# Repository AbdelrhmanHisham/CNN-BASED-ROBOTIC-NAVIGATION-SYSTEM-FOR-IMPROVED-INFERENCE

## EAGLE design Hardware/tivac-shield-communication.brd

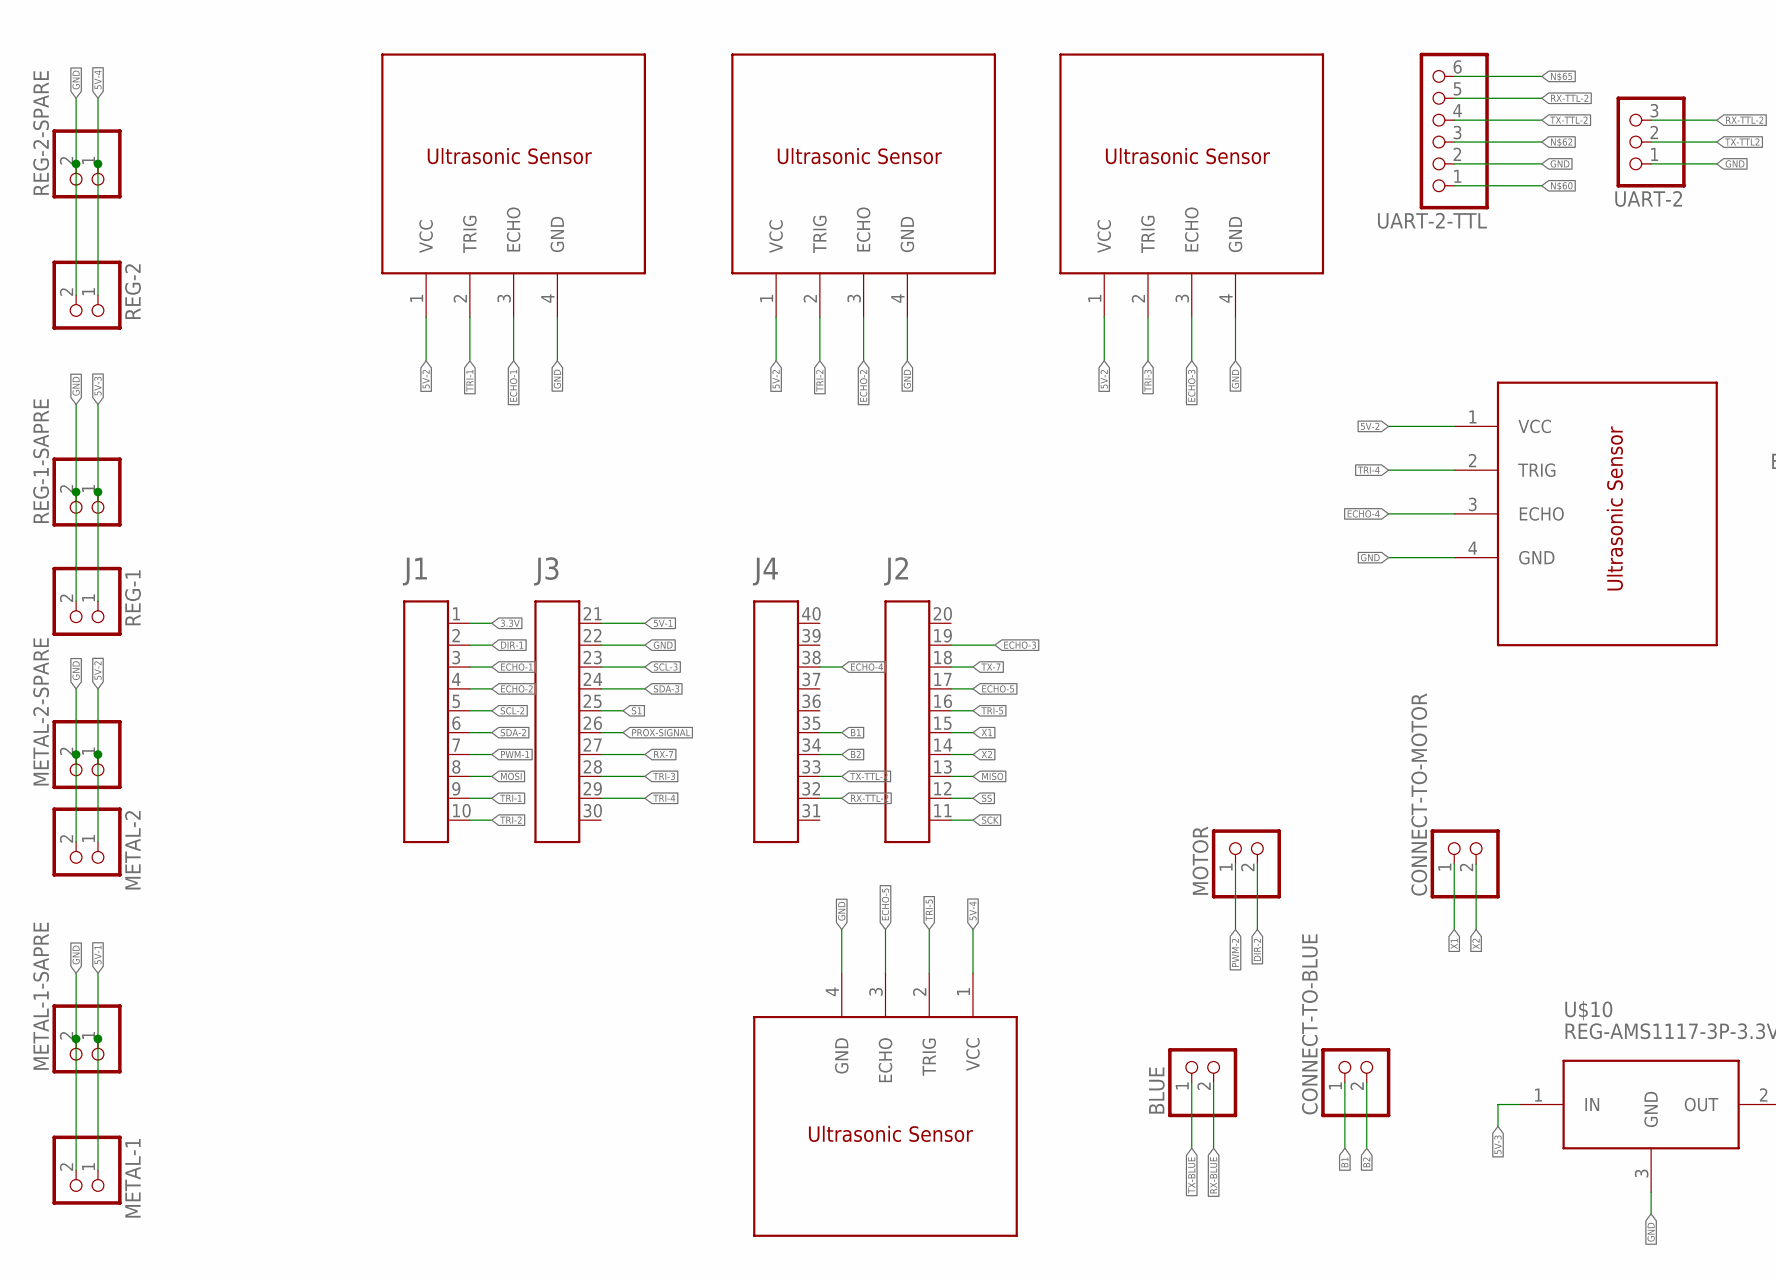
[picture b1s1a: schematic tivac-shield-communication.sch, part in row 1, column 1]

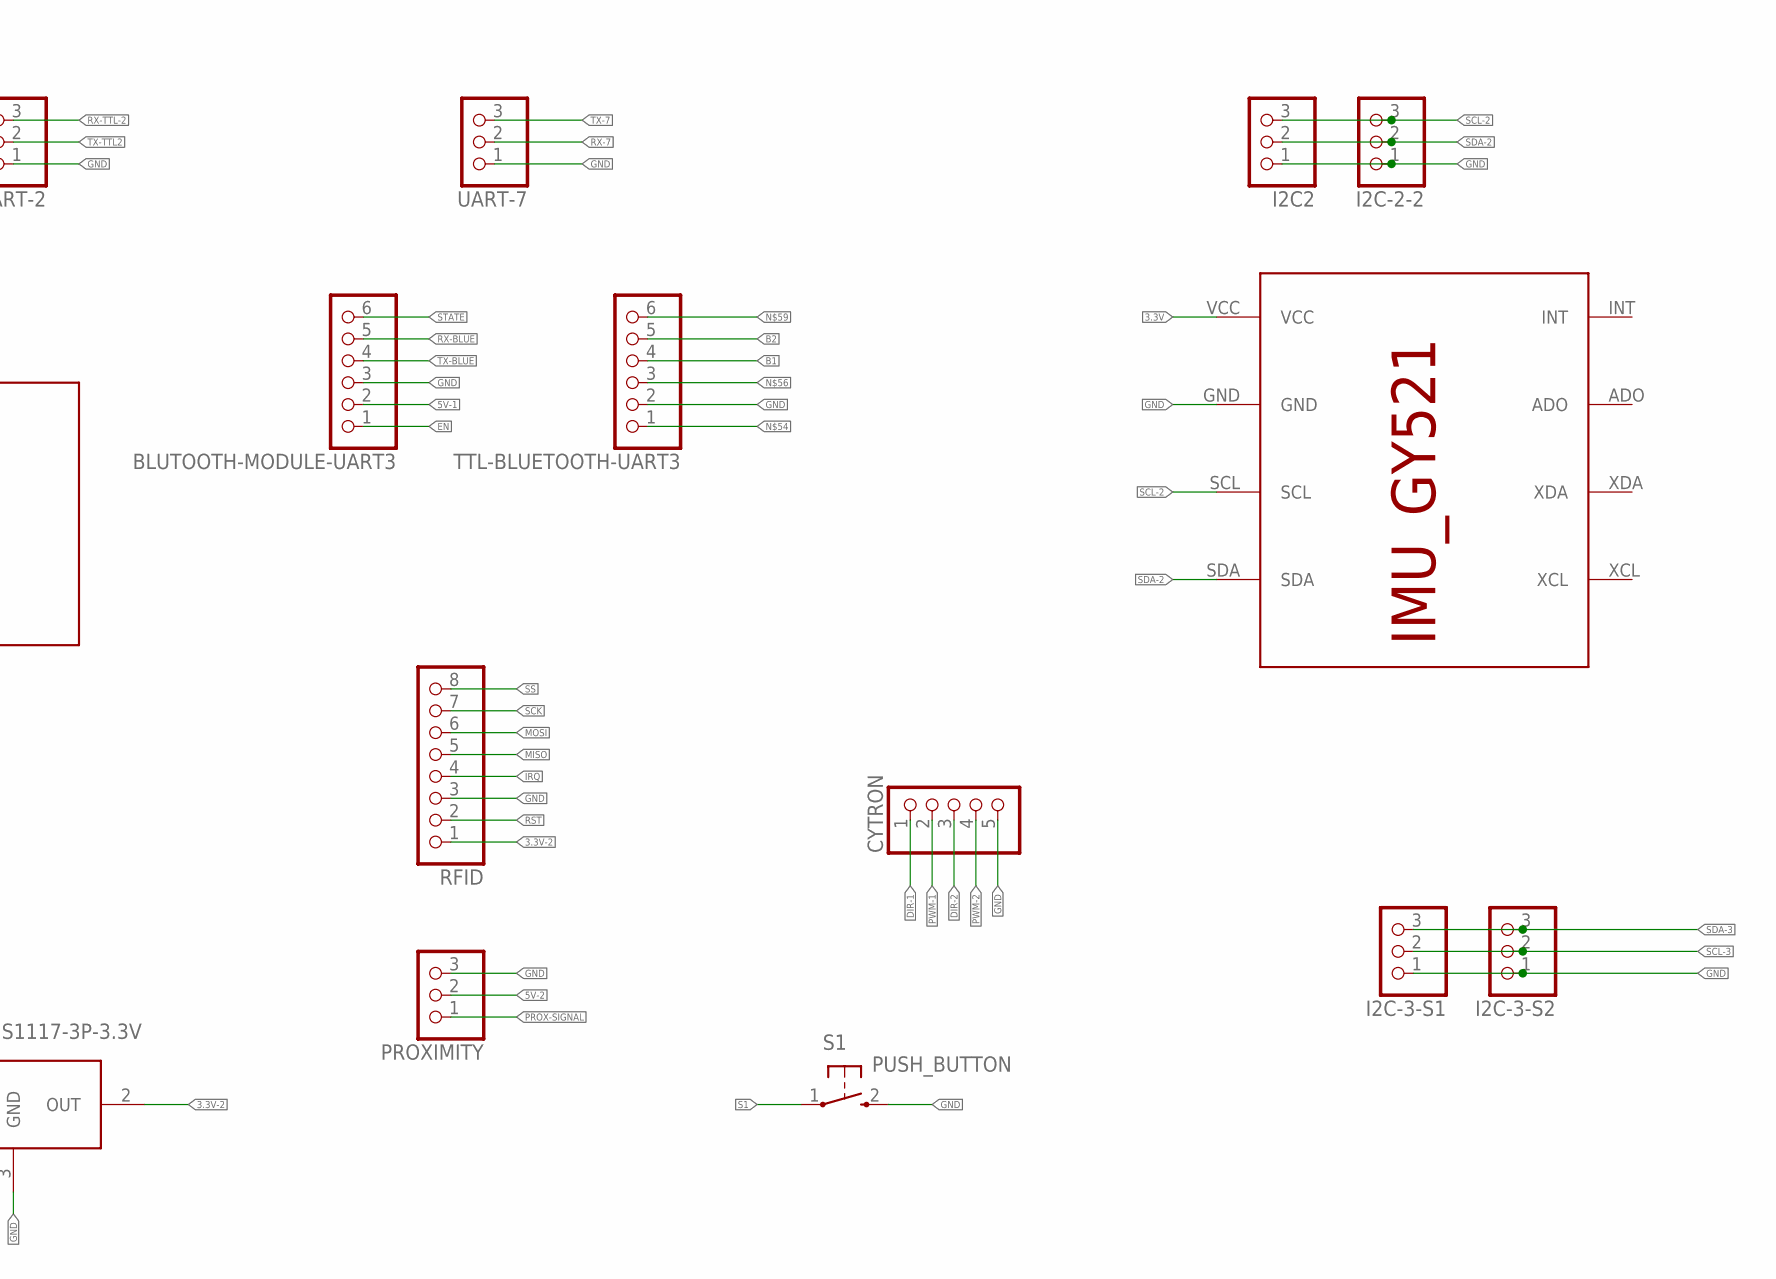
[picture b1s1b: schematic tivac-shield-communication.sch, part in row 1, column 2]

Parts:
A1: HEADER4X10-BOOSTERPACK; 4X10-BOOSTERPACK
BLUE: PINHD-2_DATA; 1X02_DATA
BLUTOOTH-MODULE-UART3: PINHD-1X6; 1X06
CONNECT-TO-BLUE: PINHD-2_DATA; 1X02_DATA
CONNECT-TO-MOTOR: PINHD-2_DATA; 1X02_DATA
CYTRON: PINHD-5_DATA; 1X05_DATA
I2C2, I2C-2-2, I2C-3-S1, I2C-3-S2: PINHD-1X3; 1X03
METAL-1, METAL-1-SAPRE, METAL-2, METAL-2-SPARE: PINHD-1X2; 1X02
MOTOR: PINHD-2_DATA; 1X02_DATA
PROXIMITY: PINHD-1X3; 1X03
REG-1, REG-1-SAPRE, REG-2, REG-2-SPARE: PINHD-1X2; 1X02
RFID: PINHD-1X8; 1X08
S1: PUSH_BUTTON; B3F-10XX
TTL-BLUETOOTH-UART3: PINHD-6_DATA; 1X06_DATA
U$1, U$2, U$3, U$5, U$7: ULTRASONIC_SENSOR; 1X04
U$9: IMU_ROBOCON; IMU_GY521
U$10: REG-AMS1117-3P-3.3V; REG-AMS1117-3P
UART-2, UART-7: PINHD-1X3; 1X03
UART-2-TTL: PINHD-6_DATA; 1X06_DATA

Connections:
3.3V: A1.1, U$9.VCC
3.3V-2: RFID.1, U$10.2 (OUT)
5V-1: A1.21, BLUTOOTH-MODULE-UART3.2, METAL-1.1, METAL-1-SAPRE.1
5V-2: METAL-2.1, METAL-2-SPARE.1, PROXIMITY.2, U$1.1 (VCC), U$2.1 (VCC), U$3.1 (VCC), U$7.1 (VCC)
5V-3: REG-1.1, REG-1-SAPRE.1, U$10.1 (IN)
5V-4: REG-2.1, REG-2-SPARE.1, U$5.1 (VCC)
B1: A1.35, CONNECT-TO-BLUE.1, TTL-BLUETOOTH-UART3.4
B2: A1.34, CONNECT-TO-BLUE.2, TTL-BLUETOOTH-UART3.5
DIR-1: A1.2, CYTRON.1
DIR-2: CYTRON.3, MOTOR.2
ECHO-1: A1.3, U$1.3 (ECHO)
ECHO-2: A1.4, U$2.3 (ECHO)
ECHO-3: A1.19, U$3.3 (ECHO)
ECHO-4: A1.38, U$7.3 (ECHO)
ECHO-5: A1.17, U$5.3 (ECHO)
EN: BLUTOOTH-MODULE-UART3.1
GND: A1.22, BLUTOOTH-MODULE-UART3.3, CYTRON.5, I2C2.1, I2C-2-2.1, I2C-3-S1.1, I2C-3-S2.1, METAL-1.2, METAL-1-SAPRE.2, METAL-2.2, METAL-2-SPARE.2, PROXIMITY.3, REG-1.2, REG-1-SAPRE.2, REG-2.2, REG-2-SPARE.2, RFID.3, S1.2 (S), TTL-BLUETOOTH-UART3.2, U$1.4 (GND), U$2.4 (GND), U$3.4 (GND), U$5.4 (GND), U$7.4 (GND), U$9.GND, U$10.3 (GND), UART-2.1, UART-2-TTL.2, UART-7.1
IRQ: RFID.4
MISO: A1.13, RFID.5
MOSI: A1.8, RFID.6
PROX-SIGNAL: A1.26, PROXIMITY.1
PWM-1: A1.7, CYTRON.2
PWM-2: CYTRON.4, MOTOR.1
RST: RFID.2
RX-7: A1.27, UART-7.2
RX-BLUE: BLUE.2, BLUTOOTH-MODULE-UART3.5
RX-TTL-2: A1.32, UART-2.3, UART-2-TTL.5
S1: A1.25, S1.1
SCK: A1.11, RFID.7
SCL-2: A1.5, I2C2.3, I2C-2-2.3, U$9.SCL
SCL-3: A1.23, I2C-3-S1.2, I2C-3-S2.2
SDA-2: A1.6, I2C2.2, I2C-2-2.2, U$9.SDA
SDA-3: A1.24, I2C-3-S1.3, I2C-3-S2.3
SS: A1.12, RFID.8
STATE: BLUTOOTH-MODULE-UART3.6
TRI-1: A1.9, U$1.2 (TRIG)
TRI-2: A1.10, U$2.2 (TRIG)
TRI-3: A1.28, U$3.2 (TRIG)
TRI-4: A1.29, U$7.2 (TRIG)
TRI-5: A1.16, U$5.2 (TRIG)
TX-7: A1.18, UART-7.3
TX-BLUE: BLUE.1, BLUTOOTH-MODULE-UART3.4
TX-TTL2: UART-2.2
TX-TTL-2: A1.33, UART-2-TTL.4
X1: A1.15, CONNECT-TO-MOTOR.1
X2: A1.14, CONNECT-TO-MOTOR.2

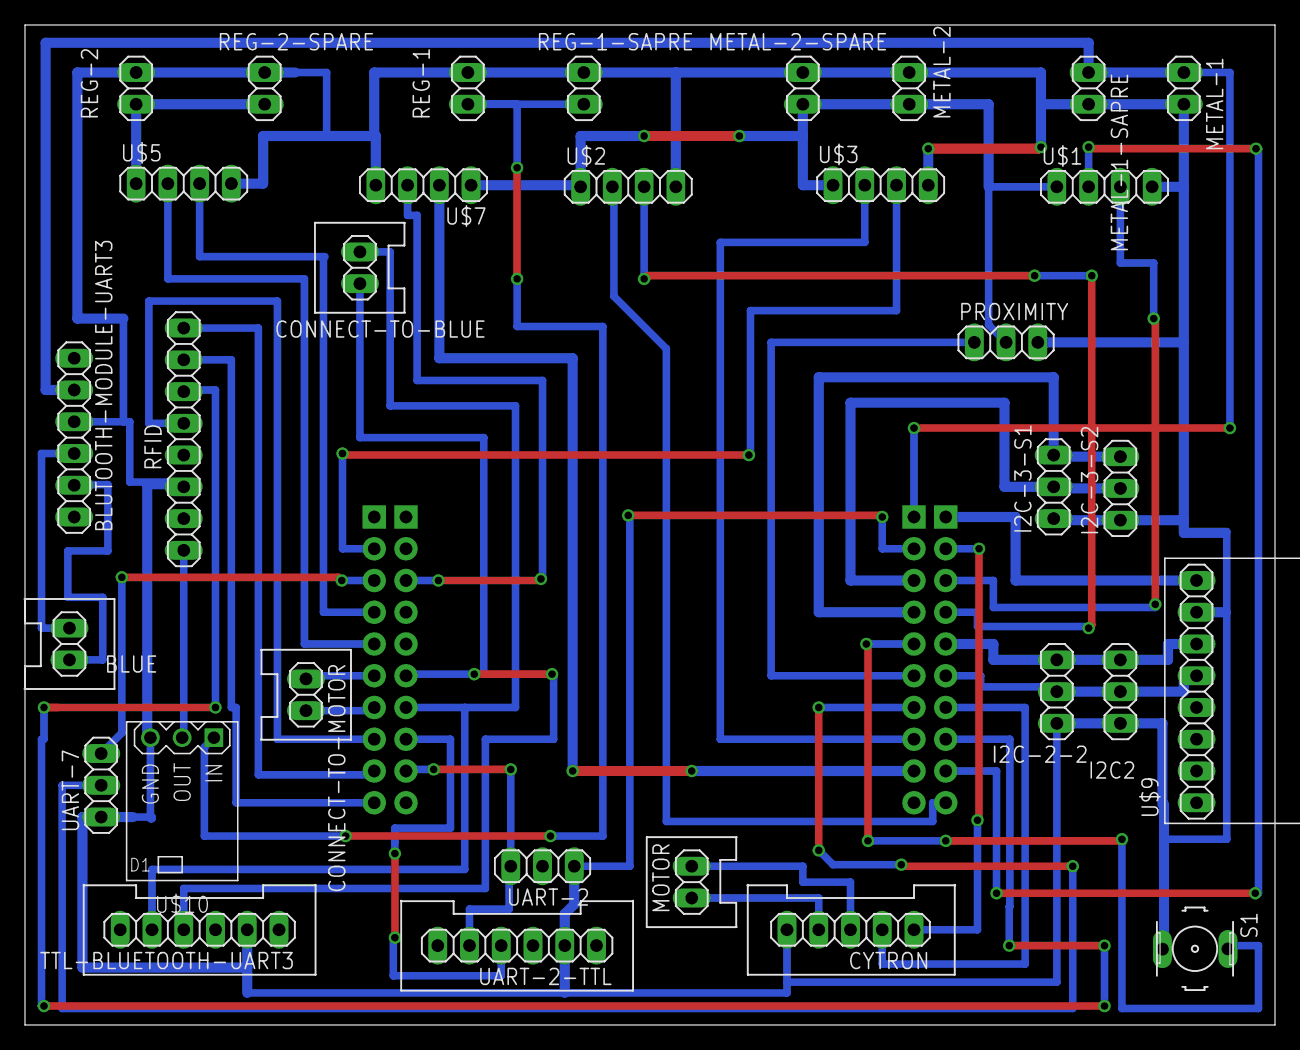
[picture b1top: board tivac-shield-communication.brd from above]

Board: 2 copper layers, 100.0 x 80.0 mm, 33 parts (1 on the bottom side), 41 nets.

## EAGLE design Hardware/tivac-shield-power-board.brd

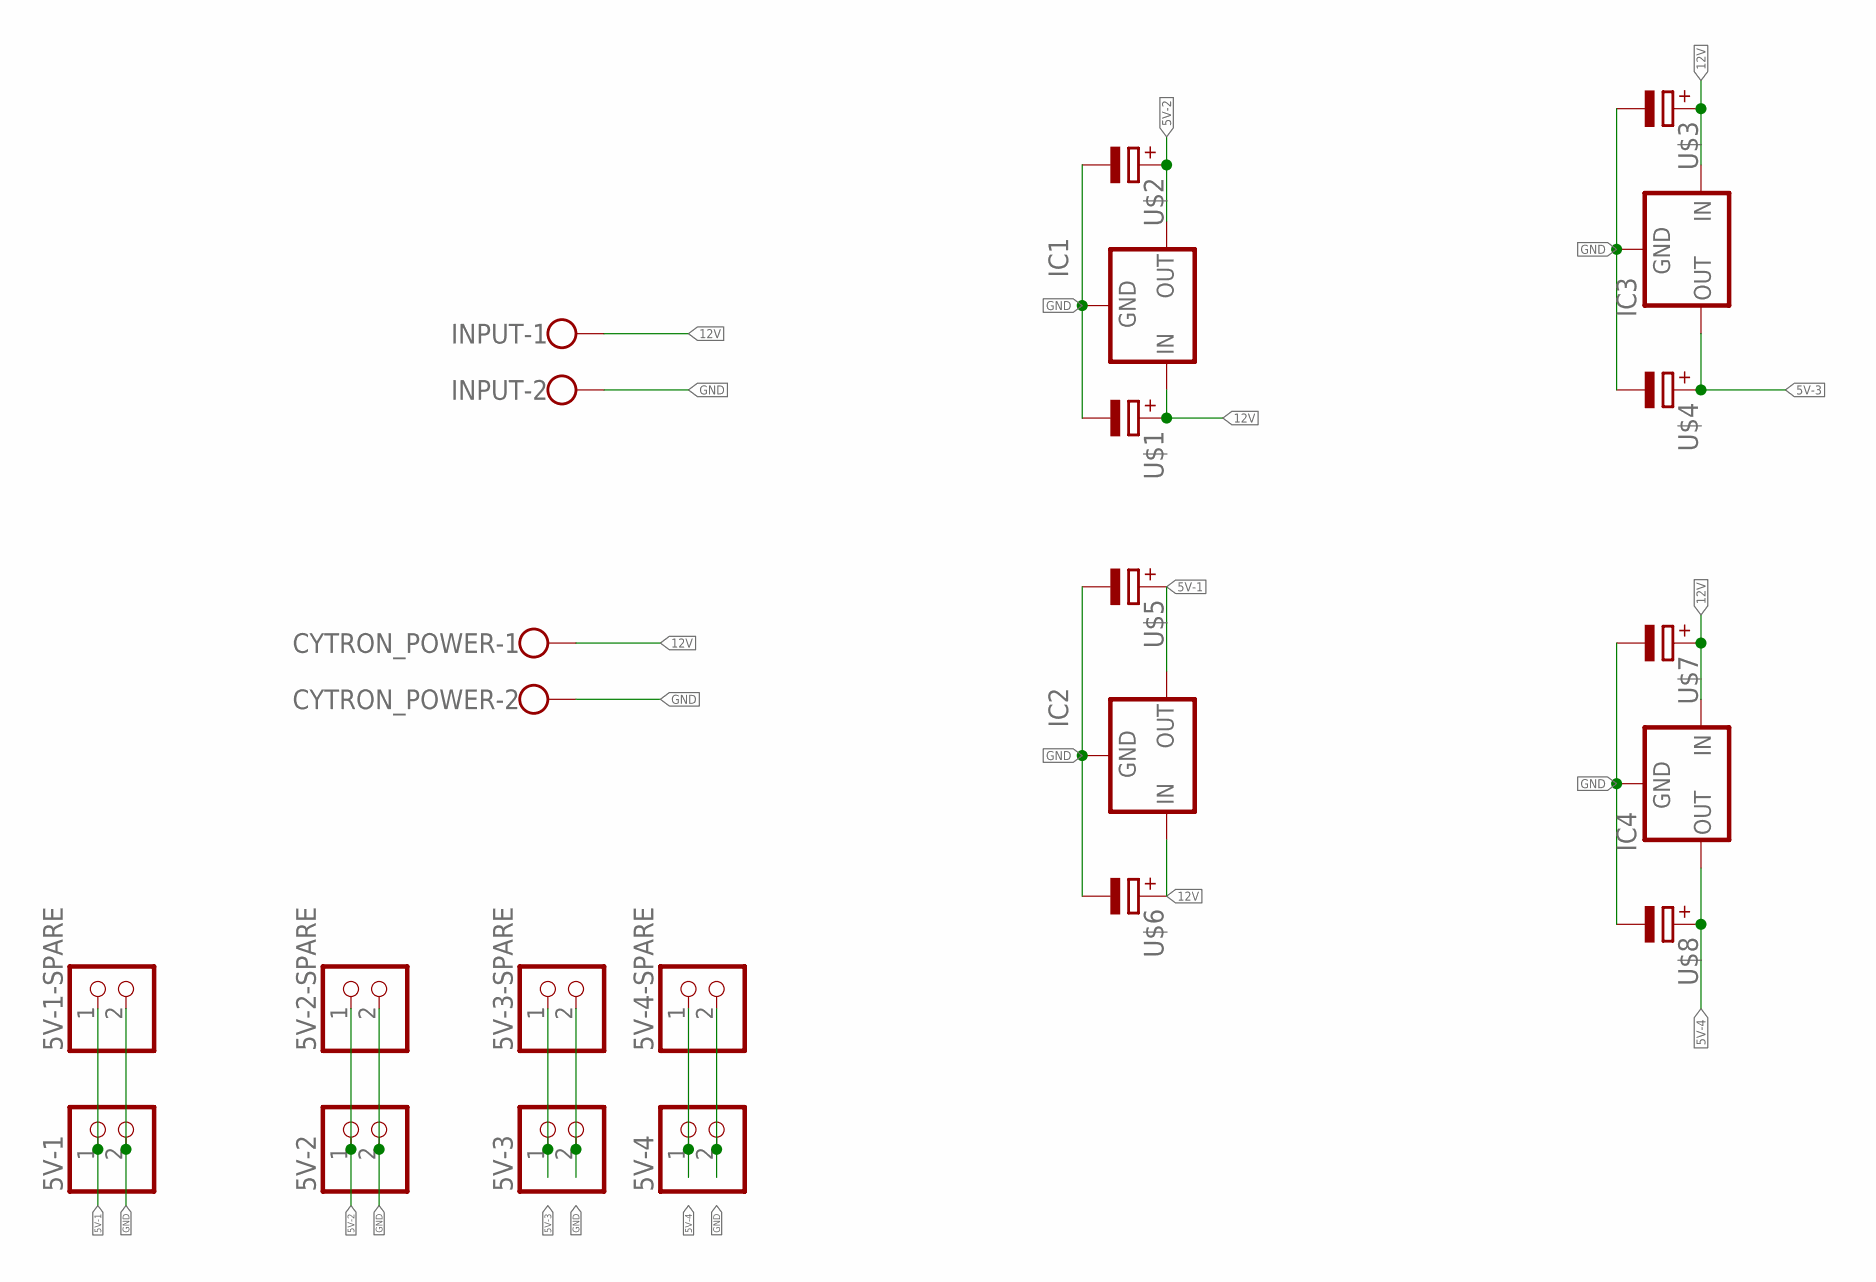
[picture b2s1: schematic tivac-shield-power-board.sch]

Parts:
5V-1, 5V-1-SPARE, 5V-2, 5V-2-SPARE, 5V-3, 5V-3-SPARE, 5V-4, 5V-4-SPARE: PINHD-1X2; 1X02
CYTRON_POWER: W237-113
IC1, IC2: 78XX-METAL; TO3-79
IC3, IC4: 78XXS
INPUT: W237-113
U$1, U$2, U$3, U$4, U$5, U$6, U$7, U$8: CAP_POL; E3,5-8

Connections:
5V-1: 5V-1.1, 5V-1-SPARE.1, IC2.1 (OUT), U$5.+
5V-2: 5V-2.1, 5V-2-SPARE.1, IC1.1 (OUT), U$2.+
5V-3: 5V-3.1, 5V-3-SPARE.1, IC3.OUT, U$4.+
5V-4: 5V-4.1, 5V-4-SPARE.1, IC4.OUT, U$8.+
12V: CYTRON_POWER.1, IC1.3 (IN), IC2.3 (IN), IC3.IN, IC4.IN, INPUT.1, U$1.+, U$3.+, U$6.+, U$7.+
GND: 5V-1.2, 5V-1-SPARE.2, 5V-2.2, 5V-2-SPARE.2, 5V-3.2, 5V-3-SPARE.2, 5V-4.2, 5V-4-SPARE.2, CYTRON_POWER.2, IC1.2 (GND), IC2.2 (GND), IC3.GND, IC4.GND, INPUT.2, U$1.-, U$2.-, U$3.-, U$4.-, U$5.-, U$6.-, U$7.-, U$8.-

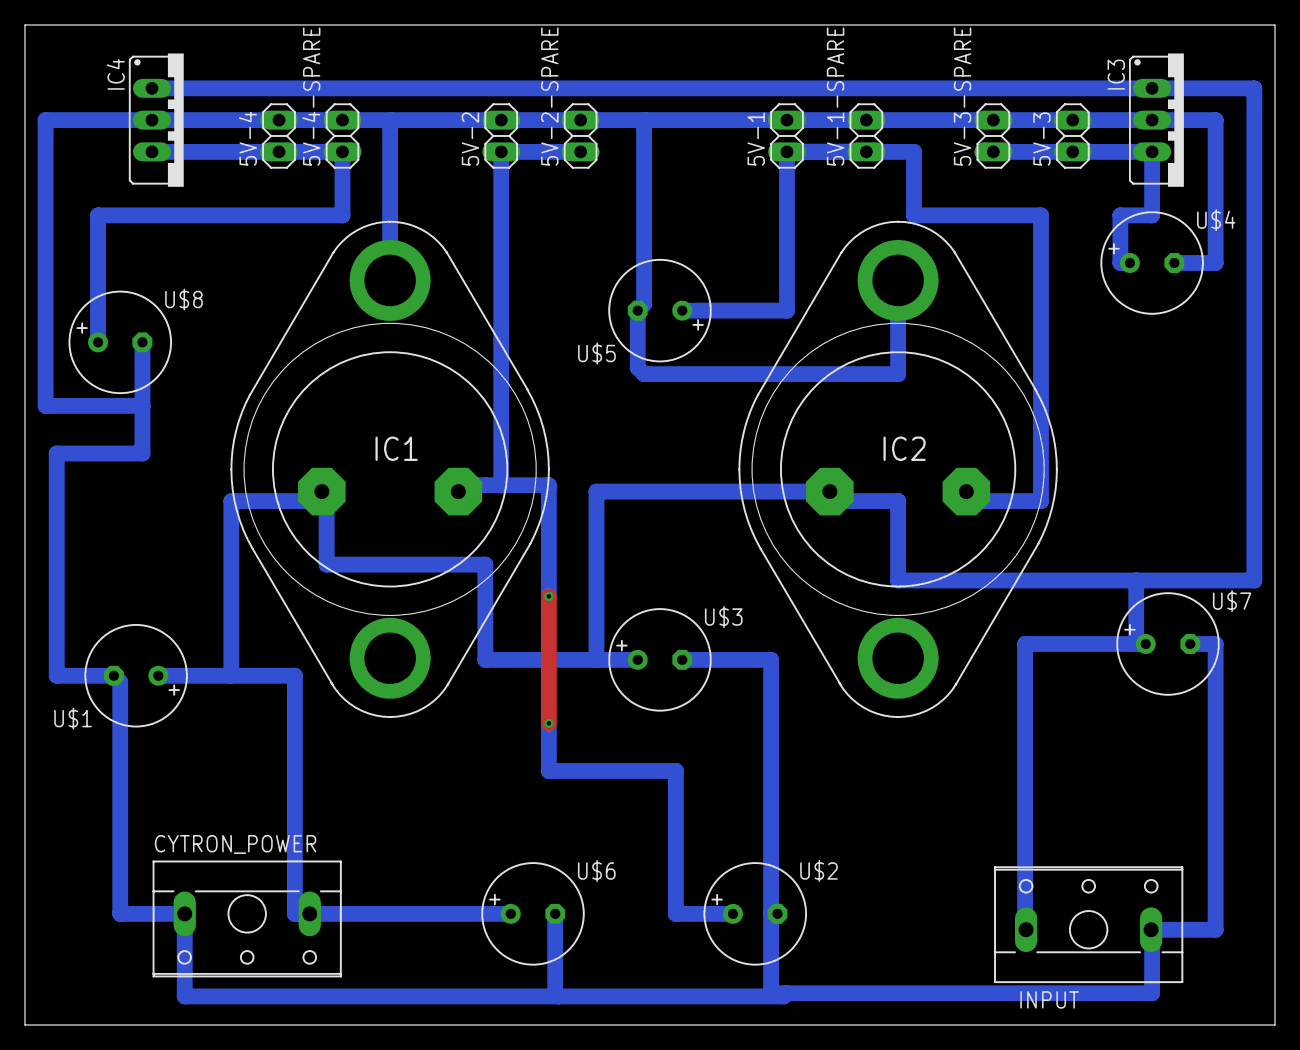
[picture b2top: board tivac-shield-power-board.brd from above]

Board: 2 copper layers, 100.0 x 80.0 mm, 22 parts (0 on the bottom side), 6 nets.

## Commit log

2020-08-10 Create embedded system
2020-08-10 mainApp
2020-08-10 Abdelrhman
